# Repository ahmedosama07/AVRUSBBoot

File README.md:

# AVRUSBBoot
USB bootloader for Atmel AVR controllers

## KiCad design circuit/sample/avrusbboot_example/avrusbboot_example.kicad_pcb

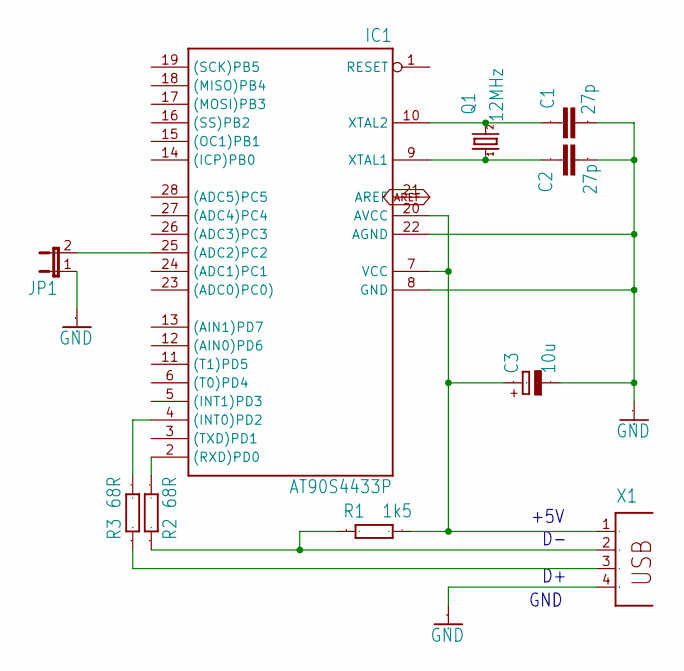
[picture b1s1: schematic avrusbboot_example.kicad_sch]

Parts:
C1, C2: 27p; C025-024X044
C3: 10u; E2,5-5
IC1: AT90S4433P; DIL28-3
JP1: JP1E; JP1
Q1: 12MHz; HC49_S
R1: 1k5; 0207_7
R2, R3: 68R; 0207_7
X1: PN61729

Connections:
AREF: IC1.21 (AREF)
D_N: R1.1, R2.1, X1.2
D_P: R3.1, X1.3
GND: C1.2, C2.2, C3.-, IC1.8 (GND), IC1.22 (AGND), JP1.1, X1.4
unnamed: IC1.25 ((ADC2)PC2), JP1.2
unnamed: C1.1, IC1.10 (XTAL2), Q1.2
unnamed: C2.1, IC1.9 (XTAL1), Q1.1
R_N: IC1.2 ((RXD)PD0), R2.2
R_P: IC1.4 ((INT0)PD2), R3.2
VCC: C3.+, IC1.7 (VCC), IC1.20 (AVCC), R1.2, X1.1

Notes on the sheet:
+5V
GND

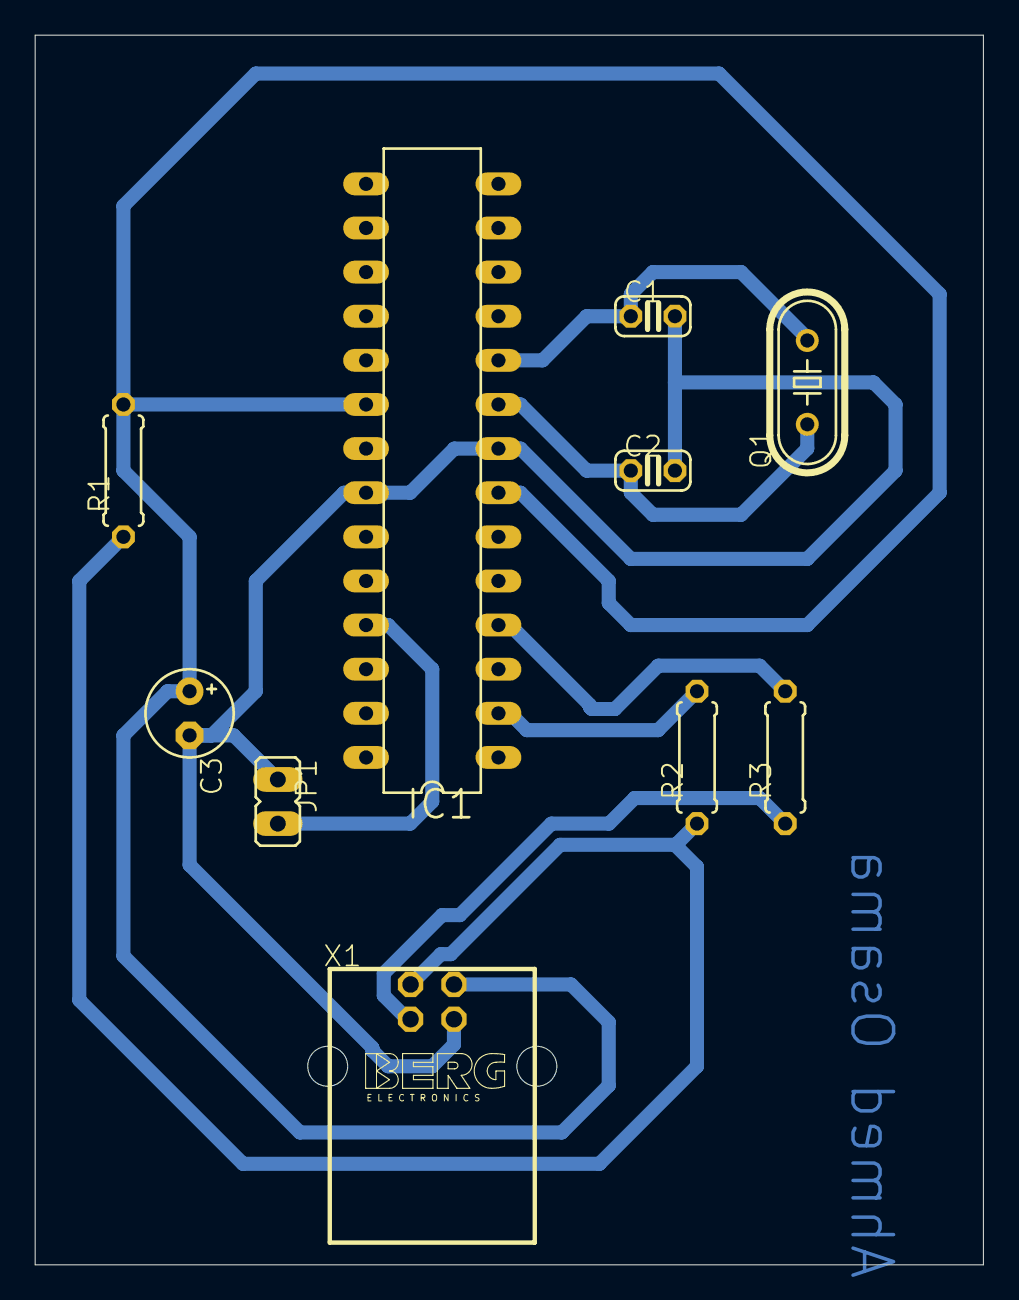
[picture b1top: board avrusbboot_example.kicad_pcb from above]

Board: 2 copper layers, 54.6 x 70.8 mm, 10 parts (0 on the bottom side), 9 nets.

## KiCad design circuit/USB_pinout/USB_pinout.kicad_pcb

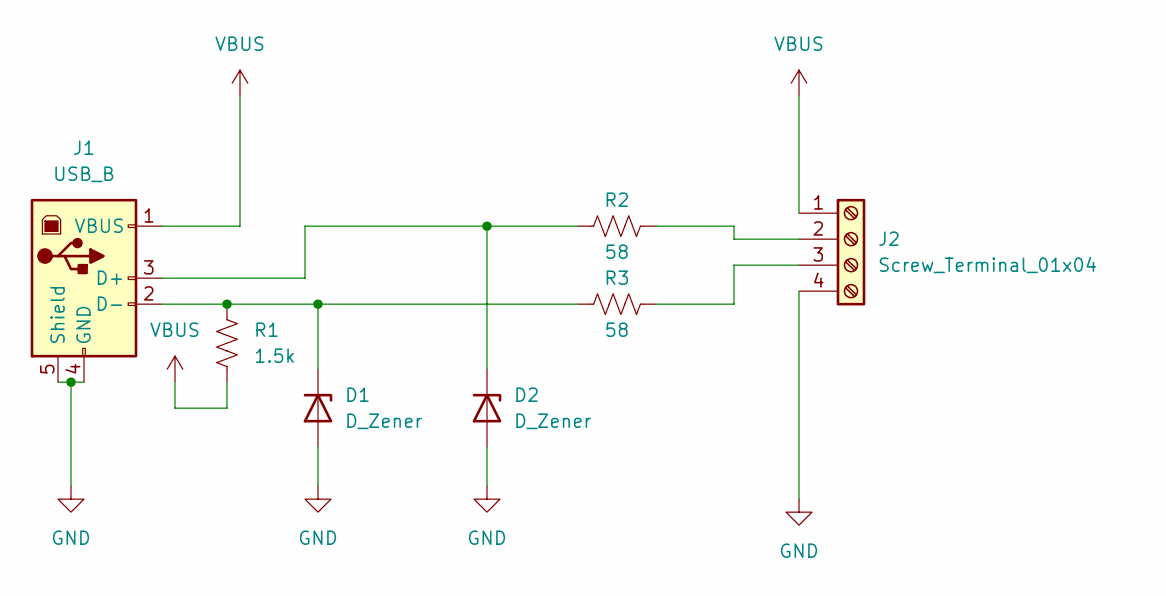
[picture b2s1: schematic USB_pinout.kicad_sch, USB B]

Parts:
D1, D2: D_Zener; D_5W_P10.16mm_Horizontal
J1: USB_B; USB_B_Lumberg_2411_02_Horizontal
J2: Screw_Terminal_01x04; JST_B4B-XH-A
R1: 1.5k; R_Axial_DIN0614_L14.3mm_D5.7mm_P15.24mm_Horizontal
R2, R3: 58; R_Axial_DIN0614_L14.3mm_D5.7mm_P15.24mm_Horizontal

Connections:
GND: D1.2 (A), D2.2 (A), J1.4 (GND), J1.5 (Shield), J2.4
unnamed: D1.1 (K), J1.2 (D-), R1.1, R3.1
unnamed: D2.1 (K), J1.3 (D+), R2.1
unnamed: J2.2, R2.2
unnamed: J2.3, R3.2
VBUS: J1.1 (VBUS), J2.1, R1.2

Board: 2 copper layers, 7 parts (0 on the bottom side), 6 nets, no tracks yet.

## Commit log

2023-11-07 compiled
2023-11-27 Simple PCB
2023-11-27 sample board
2023-12-02 schematic
2023-12-02 Connectors
2023-12-03 usbasp programmer
2023-12-03 clean
2023-12-03 build
2023-12-03 routing pcb
2023-12-03 software tests
2023-12-03 pcb trial
2023-12-03 Revert "pcb trial"
    This reverts commit de32394c14970a8398b5581bec110614df603549.
2023-12-03 Revert "schematic without routing"
2023-12-04 Update issue templates
2023-12-10 fix windows error
    in Visual Studio when running this method caused an error pointed by @ziadelbouriny
2023-12-29 Windows tool
2023-12-29 update logging
2023-12-29 kicad schematics
2023-12-30 cleaning
2023-12-30 release
